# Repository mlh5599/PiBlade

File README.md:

# Pi Blade

## Description
A complete 2U blade mounting system for Raspberry Pi 1B/3/3B,4B, and 5.  Includes 2U rail mount and blades remixed from the work done by Krapozok on [Thingiverse](https://www.thingiverse.com/thing:1793758).

The lights are based on RagnarJensen's [PiLEDLights](https://github.com/RagnarJensen/PiLEDlights) project with the Wiring Pi dependency removed.  

OLED display is a work in progress.

---

---

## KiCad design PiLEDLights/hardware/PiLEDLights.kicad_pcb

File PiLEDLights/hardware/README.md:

# Pi LED Lights PCB

## Description
WIP

## Images
\

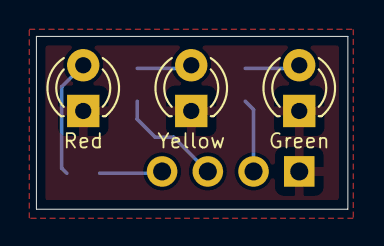
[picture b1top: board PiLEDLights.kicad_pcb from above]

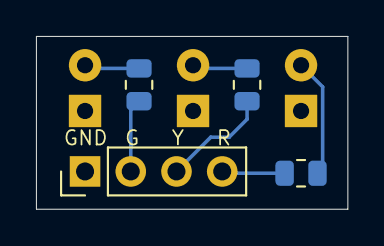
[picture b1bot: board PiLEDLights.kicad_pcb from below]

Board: 2 copper layers, 17.3 x 9.6 mm, 7 parts (4 on the bottom side), 7 nets.

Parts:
Green: LED; LED_D3.0mm
J1: Conn_01x04; PinHeader_1x04_P2.54mm_Vertical
R1, R2, R3: 100; R_0805_2012Metric
Red: LED; LED_D3.0mm
Yellow: LED; LED_D3.0mm

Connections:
unnamed: Green.2 (A), R1.2
unnamed: Green.1 (K), J1.1, Red.1 (K), Yellow.1 (K)
unnamed: R2.2, Yellow.2 (A)
unnamed: R3.2, Red.2 (A)
unnamed: J1.2, R1.1
unnamed: J1.3, R2.1
unnamed: J1.4, R3.1

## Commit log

2023-09-23 Initial commit, switching out WiringPi for pigpio.
2023-09-23 Add attribution to original project.
2023-09-23 Fix spacing in markdown
2023-09-23 More md fixes
2023-09-23 One more md fix
2023-11-22 Added intensity capability to net and hdd files
2023-11-22 Fix bug in arg_options
2023-11-22 Add missing option for intensity in arg_options
2023-11-22 And fix the missing comma :(
2024-03-02 Added tailscaleledPi
2024-03-02 Fix readme link
2024-03-02 Make tailscaleledPi a bit more efficient.
2024-12-11 Renamed to PiBlade, added rack mount system and PiLEDLights PCB
